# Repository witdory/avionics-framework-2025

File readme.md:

# Arduino rocket avionics firmware platform

This project provides a framework for Arduino to quickly build and maintain Rocket Avionics and can be expanded according to the user's intentions. Users can easily add various sensors they want to use to the Avionics system, set them to perform custom missions, and help manage mission performance by flight stage throughout the entire flight process. This is significant in that it provides an expandable avionics framework based on Arduino, which is easily accessible, instead of existing expensive avionics such as Pixhawk. In addition, it provides not only software but also hardware design that includes basic sensors needed for avionics, helping to produce a low-cost avionics system in a short time.

## feature
1. Quick and convenient sensor addition and management
2. Custom launch stages and mission control
3. Providing communication packets for efficient telemetry transmission and reception with ground stations
4. High reusability and maintainability
5. Provide hardware circuit design
6. support canard fin pid control

## software architecture

## packet architecture
In order to reduce unnecessary bit transmission during the communication process and ensure communication reliability and real-time, packets were designed and protocols were created.

Data types are classified as follows. At this time, rocketstate, cmd, etc. must transmit and receive data accurately, so like the TCP protocol, when data is received from the receiver, it sends an ACK to the transmitter. If the ACK is not received from the transmitter, it is designed to transmit the data one more time. Like sensor telemetry, it sends an ACK to the transmitter. Data where real-time is important were excluded from this process.

## uml

## hardware
The hardware basically consists of GPS, IMU, barometer, SD reader, motor, and communication module. In addition, the user can replace and add sensors as needed. The initial version of the hardware used a breadboard, and the latest version had a new PCB design to increase stability.
excluded from this process.

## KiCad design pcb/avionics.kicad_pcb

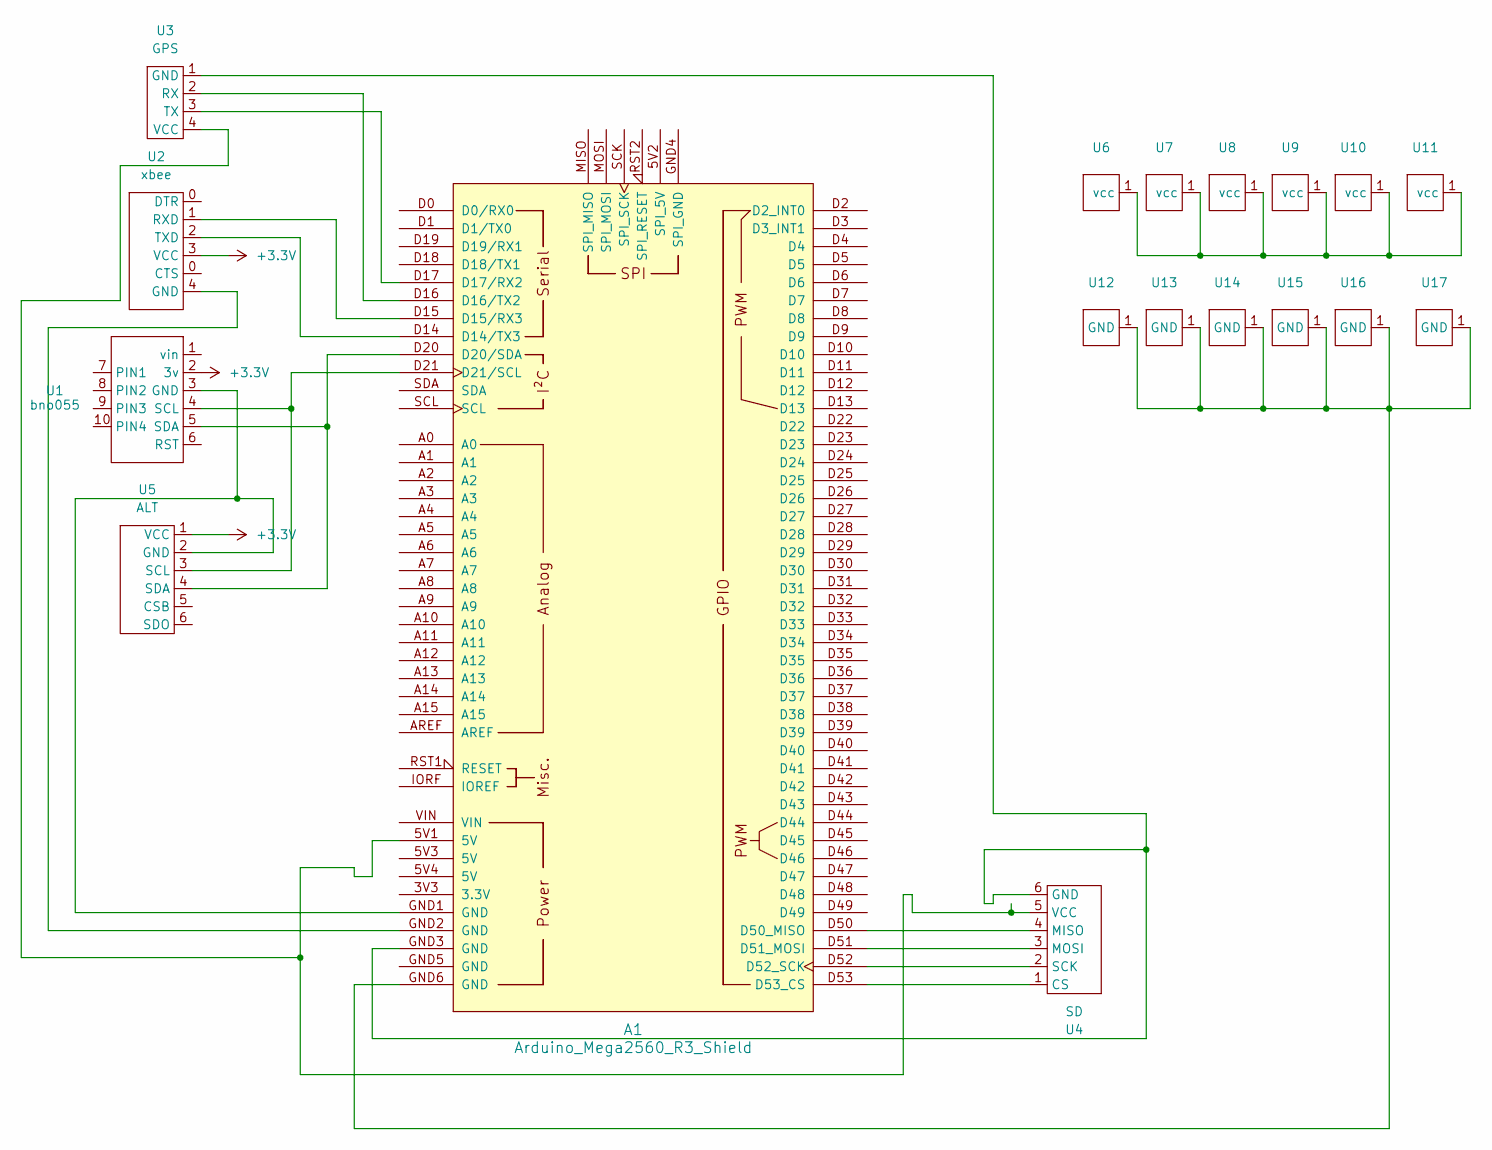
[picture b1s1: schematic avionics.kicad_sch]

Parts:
A1: Arduino_Mega2560_R3_Shield
U1: bno055
U2: xbee
U3: GPS; gps
U4: SD; sd
U5: ALT; bmp280
U6, U7, U8, U9, U10, U11: motor_vcc
U12, U13, U14, U15, U16, U17: motor_gnd

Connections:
+3.3V: U1.2 (3v), U2.3 (VCC), U5.1 (VCC)
unnamed: A1.D14 (D14/TX3), U2.2 (TXD)
unnamed: A1.D15 (D15/RX3), U2.1 (RXD)
unnamed: A1.D16 (D16/TX2), U3.2 (RX)
unnamed: A1.D17 (D17/RX2), U3.3 (TX)
unnamed: A1.D20 (D20/SDA), U1.5 (SDA), U5.4 (SDA)
unnamed: A1.D21 (D21/SCL), U1.4 (SCL), U5.3 (SCL)
unnamed: A1.D50 (D50_MISO), U4.4 (MISO)
unnamed: A1.D51 (D51_MOSI), U4.3 (MOSI)
unnamed: A1.D52 (D52_SCK), U4.2 (SCK)
unnamed: A1.D53 (D53_CS), U4.1 (CS)
unnamed: A1.GND1 (GND), U1.3 (GND), U5.2 (GND)
unnamed: A1.GND2 (GND), U2.4 (GND)
unnamed: A1.GND3 (GND), U3.1 (GND), U4.6 (GND)
unnamed: A1.5V1 (5V), U3.4 (VCC), U4.5 (VCC)
unnamed: U6.1 (vcc), U7.1 (vcc), U8.1 (vcc), U9.1 (vcc), U10.1 (vcc), U11.1 (vcc)
unnamed: A1.GND6 (GND), U12.1 (GND), U13.1 (GND), U14.1 (GND), U15.1 (GND), U16.1 (GND), U17.1 (GND)

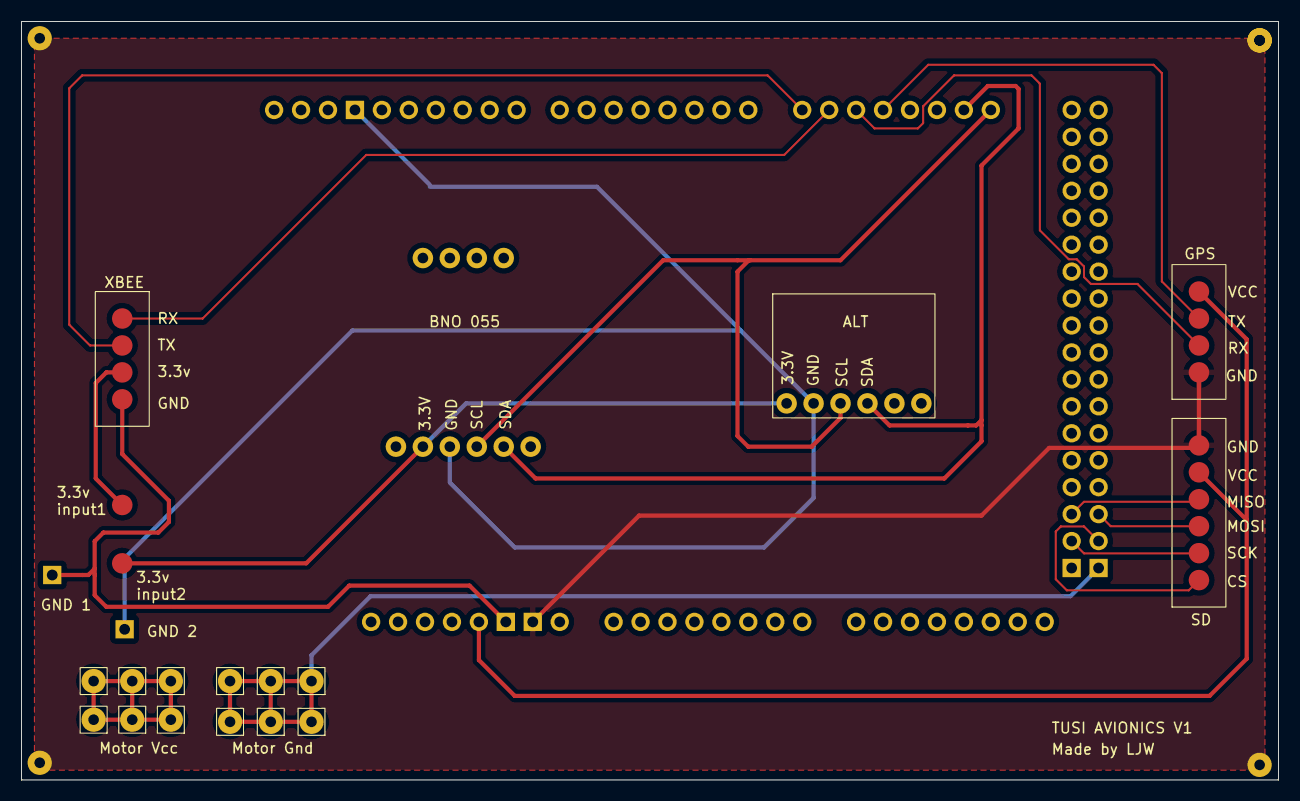
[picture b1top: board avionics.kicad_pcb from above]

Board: 2 copper layers, 118.5 x 71.5 mm, 17 parts (0 on the bottom side), 17 nets.

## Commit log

2024-11-19 first commit
2024-11-19 fix images
2024-11-19 add images
2025-07-22 feat: http 통신 기능 추가 및 retrieval stage 추가
2025-07-23 get_command 메소드 수정
2025-07-23 feat: persistent tcp 통신 적용
2025-07-23 feat: Stage 변경 기능 적용
2025-07-24 feat: stage 전환 적용
2025-07-24 fix: bmp280 오류 해결
2025-07-24 feat: Ascending, Apogee 감지 적용
2025-07-25 feat: Retrieval 감지 적용용
2025-07-25 feat: gps 정보 수신
2025-07-25 fix: gps 데이터 파싱 문제 해결
